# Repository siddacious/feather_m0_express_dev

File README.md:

# feather_m0_express_dev
Added two developer friendly features:
* SWD header for debugging
* SPI header for the on board SPI flash

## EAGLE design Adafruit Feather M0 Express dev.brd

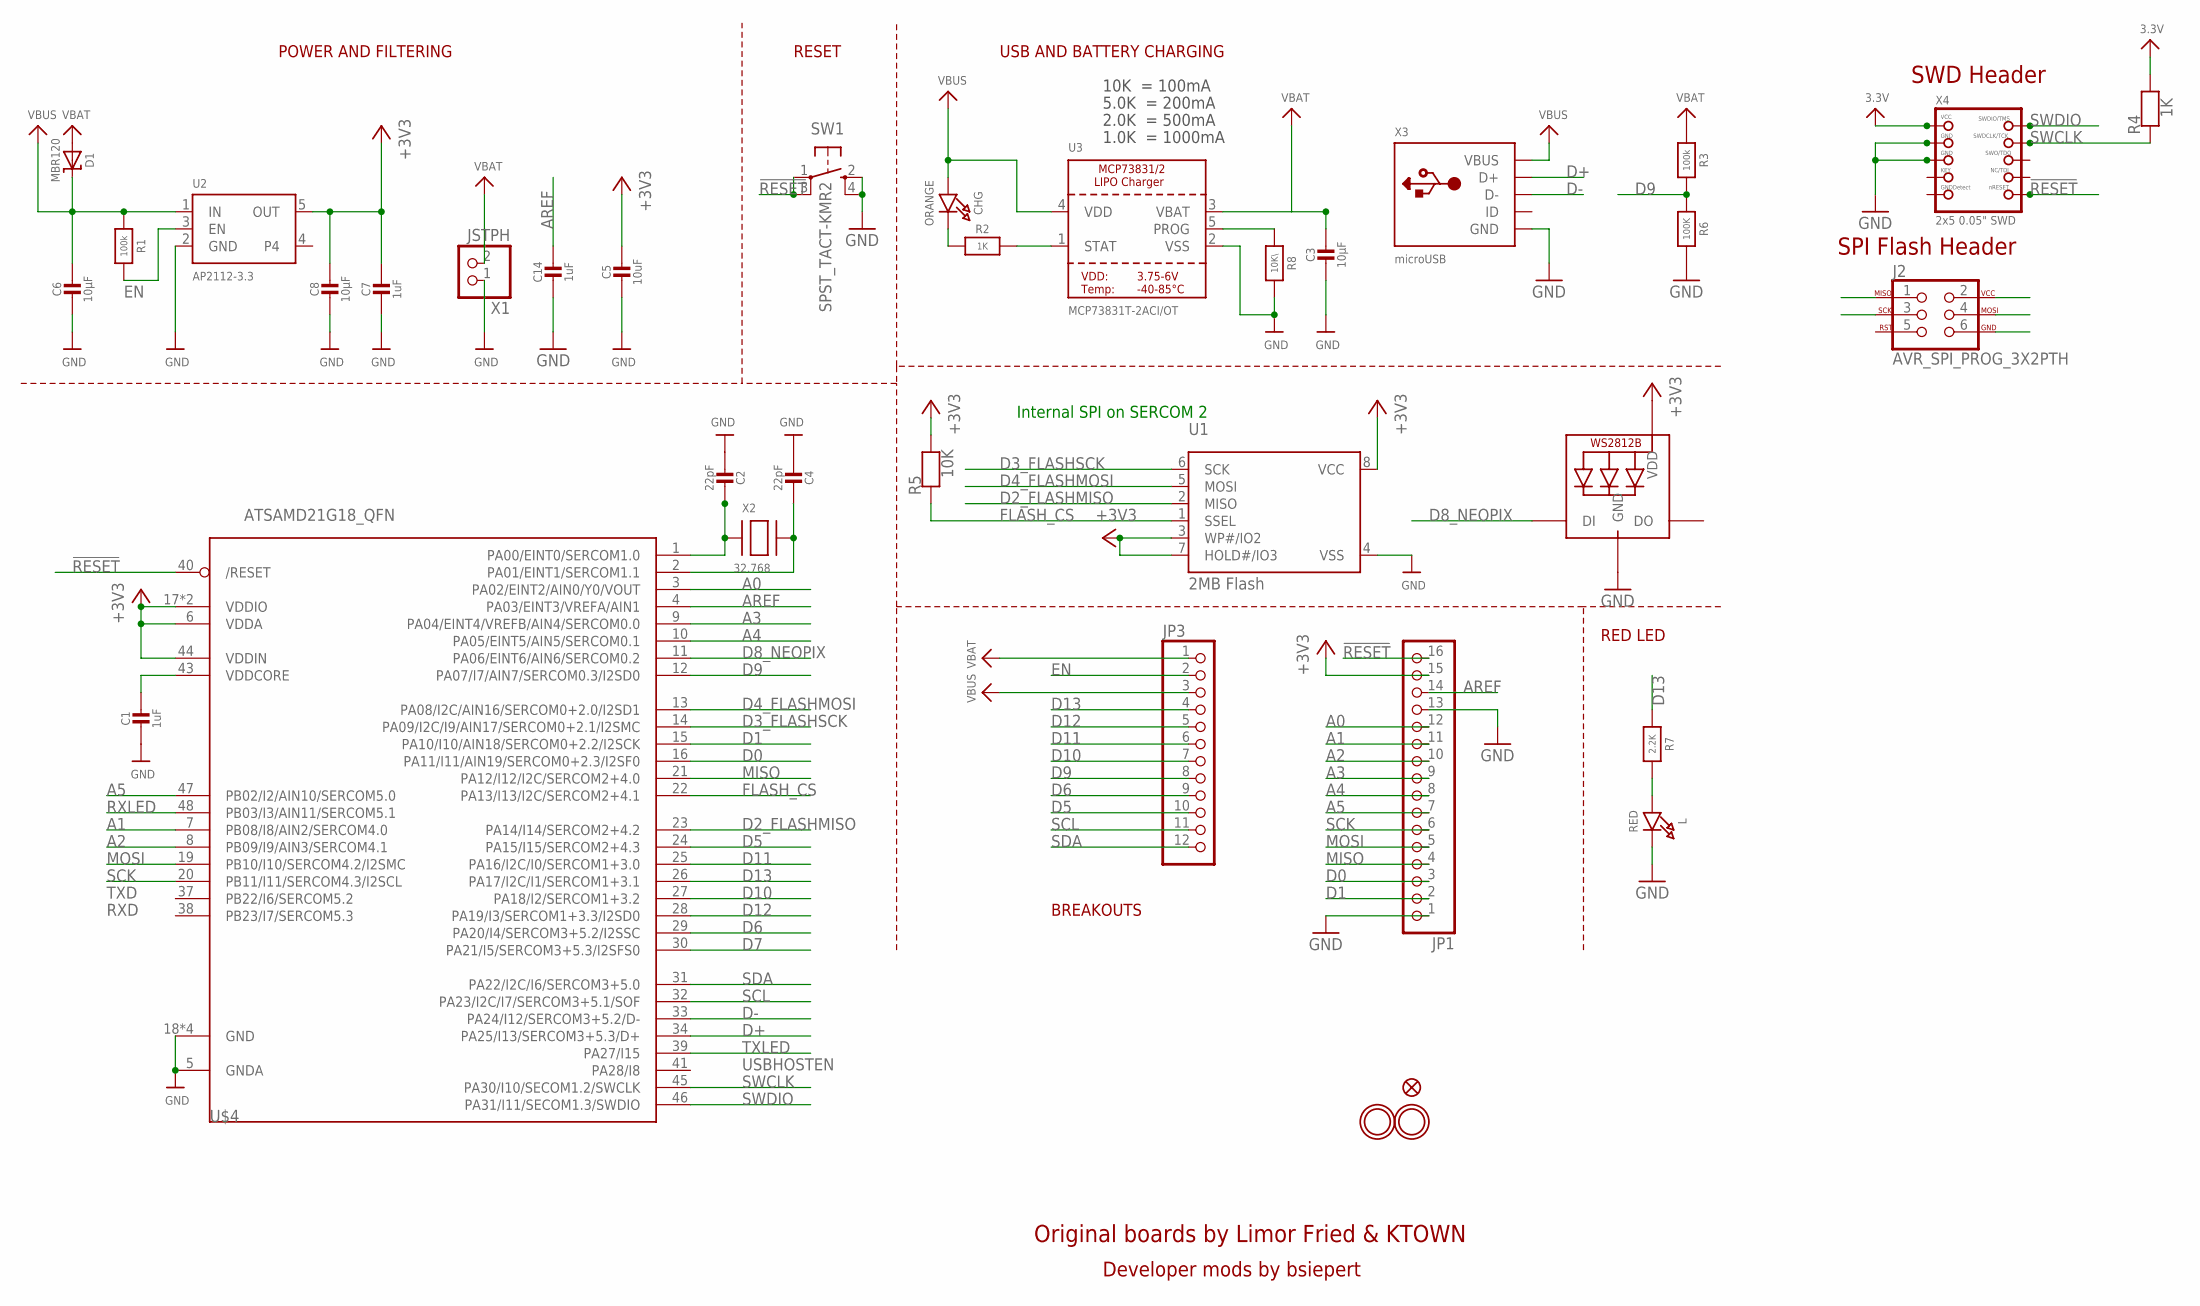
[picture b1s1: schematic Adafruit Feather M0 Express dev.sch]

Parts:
C1, C7, C14: 1uF; 0603-NO
C2, C4: 22pF; 0603-NO
C3, C6, C8: 10µF; 0805-NO
C5: 10uF; 0805-NO
CHG: ORANGE; CHIPLED_0805_NOOUTLINE
D1: MBR120; SOD-123
J2: AVR_SPI_PROG_3X2PTH; 2X3
JP1: HEADER-1X16ROUND; 1X16_ROUND
JP3: HEADER-1X12; 1X12_ROUND
L: RED; CHIPLED_0805_NOOUTLINE
LED1: WS2812B3535; LED3535
R1, R3: 100k; 0603-NO
R2: 1K; 0603-NO
R4: 1K; 0805-NO
R5: 10K; 0603-NO
R6: 100K; 0603-NO
R7: 2.2K; 0603-NO
R8: 10K\; 0603-NO
SW1: SPST_TACT-KMR2; KMR2
U1: 2MB Flash; SOIC8_208MIL
U2: AP2112-3.3; SOT23-5
U3: MCP73831T-2ACI/OT; SOT23-5
U$4: ATSAMD21G18_QFN; TQFN48_7MM
U$31, U$32: MOUNTINGHOLE2.5; MOUNTINGHOLE_2.5_PLATED
U$34: FIDUCIAL""; FIDUCIAL_1MM
X1: JSTPH; JSTPH2
X2: 32.768; XTAL3215
X3: microUSB; 4UCONN_20329_V2
X4: 2x5 0.05" SWD; 2X05_1.27MM_BOX_POSTS

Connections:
!RESET: JP1.16, SW1.1, SW1.3 (P1), U$4.40 (/RESET), X4.10 (NRESET)
+3V3: C5.1, C7.1, C8.1, J2.2, JP1.15, LED1.2 (VDD), R4.2, R5.2, U1.3 (WP#/IO2), U1.7 (HOLD#/IO3), U1.8 (VCC), U2.5 (OUT), U$4.6 (VDDA), U$4.17 (VDDIO), U$4.36 (VDDIO), U$4.44 (VDDIN), X4.1 (VCC)
A0: JP1.12, U$4.3 (PA02/EINT2/AIN0/Y0/VOUT)
A1: JP1.11, U$4.7 (PB08/I8/AIN2/SERCOM4.0)
A2: JP1.10, U$4.8 (PB09/I9/AIN3/SERCOM4.1)
A3: JP1.9, U$4.9 (PA04/EINT4/VREFB/AIN4/SERCOM0.0)
A4: JP1.8, U$4.10 (PA05/EINT5/AIN5/SERCOM0.1)
A5: JP1.7, U$4.47 (PB02/I2/AIN10/SERCOM5.0)
AREF: C14.1, JP1.14, U$4.4 (PA03/EINT3/VREFA/AIN1)
D0: JP1.3, U$4.16 (PA11/I11/AIN19/SERCOM0+2.3/I2SF0)
D1: JP1.2, U$4.15 (PA10/I10/AIN18/SERCOM0+2.2/I2SCK)
D2_FLASHMISO: J2.1, U1.2 (MISO), U$4.23 (PA14/I14/SERCOM2+4.2)
D3_FLASHSCK: J2.3, U1.6 (SCK), U$4.14 (PA09/I2C/I9/AIN17/SERCOM0+2.1/I2SMC)
D4_FLASHMOSI: J2.4, U1.5 (MOSI), U$4.13 (PA08/I2C/AIN16/SERCOM0+2.0/I2SD1)
D5: JP3.10, U$4.24 (PA15/I15/SERCOM2+4.3)
D6: JP3.9, U$4.29 (PA20/I4/SERCOM3+5.2/I2SSC)
D7: U$4.30 (PA21/I5/SERCOM3+5.3/I2SFS0)
D8_NEOPIX: LED1.1 (DI), U$4.11 (PA06/EINT6/AIN6/SERCOM0.2)
D9: JP3.8, R3.2, R6.1, U$4.12 (PA07/I7/AIN7/SERCOM0.3/I2SD0)
D10: JP3.7, U$4.27 (PA18/I2/SERCOM1+3.2)
D11: JP3.6, U$4.25 (PA16/I2C/I0/SERCOM1+3.0)
D12: JP3.5, U$4.28 (PA19/I3/SERCOM1+3.3/I2SD0)
D13: JP3.4, R7.1, U$4.26 (PA17/I2C/I1/SERCOM1+3.1)
D+: U$4.34 (PA25/I13/SERCOM3+5.3/D+), X3.D+
D-: U$4.33 (PA24/I12/SERCOM3+5.2/D-), X3.D-
EN: JP3.2, R1.2, U2.3 (EN)
FLASH_CS: R5.1, U1.1 (SSEL), U$4.22 (PA13/I13/I2C/SERCOM2+4.1)
GND: C1.2, C2.2, C3.2, C4.2, C5.2, C6.2, C7.2, C8.2, C14.2, J2.6, JP1.1, JP1.13, L.C, LED1.4 (GND), R6.2, R8.2, SW1.2 (S), SW1.4 (S1), U1.4 (VSS), U2.2 (GND), U3.2 (VSS), U$4.5 (GNDA), U$4.18 (GND), U$4.35 (GND), U$4.42 (GND), U$4.THERMAL (GND), X1.1, X3.BASE@1 (GND), X3.BASE@2 (GND), X3.GND, X3.SPRT@1 (GND), X3.SPRT@2 (GND), X3.SPRT@3 (GND), X3.SPRT@4 (GND), X4.3 (GND), X4.5 (GND)
MISO: JP1.4, U$4.21 (PA12/I12/I2C/SERCOM2+4.0)
MOSI: JP1.5, U$4.19 (PB10/I10/SERCOM4.2/I2SMC)
unnamed: CHG.C, R2.1
unnamed: L.A, R7.2
unnamed: R2.2, U3.1 (STAT)
unnamed: R8.1, U3.5 (PROG)
unnamed: C2.1, U$4.1 (PA00/EINT0/SERCOM1.0), X2.P$1
unnamed: C4.1, U$4.2 (PA01/EINT1/SERCOM1.1), X2.P$2
RXLED: U$4.48 (PB03/I3/AIN11/SERCOM5.1)
SCK: JP1.6, U$4.20 (PB11/I11/SERCOM4.3/I2SCL)
SCL: JP3.11, U$4.32 (PA23/I2C/I7/SERCOM3+5.1/SOF)
SDA: JP3.12, U$4.31 (PA22/I2C/I6/SERCOM3+5.0)
SWCLK: R4.1, U$4.45 (PA30/I10/SECOM1.2/SWCLK), X4.4 (SWDCLK)
SWDIO: U$4.46 (PA31/I11/SECOM1.3/SWDIO), X4.2 (SWDIO)
TXLED: U$4.39 (PA27/I15)
VBAT: C3.1, D1.A, JP3.1, R3.1, U3.3 (VBAT), X1.2
VBUS: C6.1, CHG.A, D1.C, JP3.3, R1.1, U2.1 (IN), U3.4 (VDD), X3.VBUS
VDDCORE: C1.1, U$4.43 (VDDCORE)

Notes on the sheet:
POWER AND FILTERING
RESET
10K = 100mA
5.0K = 200mA
2.0K = 500mA
1.0K = 1000mA
USBHOSTEN
TXD
RXD
USB AND BATTERY CHARGING
BREAKOUTS
RED LED
Internal SPI on SERCOM 2
Original boards by Limor Fried & KTOWN
SWD Header
Developer mods by bsiepert
SPI Flash Header

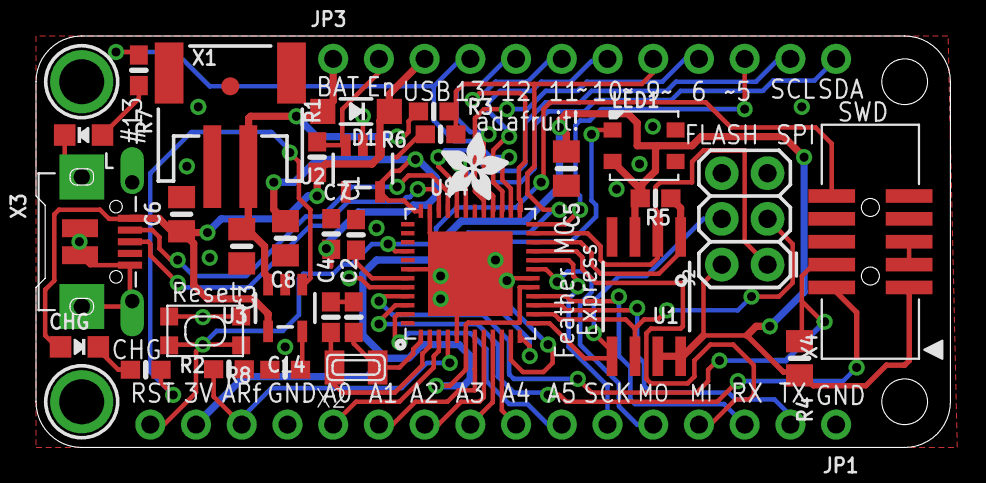
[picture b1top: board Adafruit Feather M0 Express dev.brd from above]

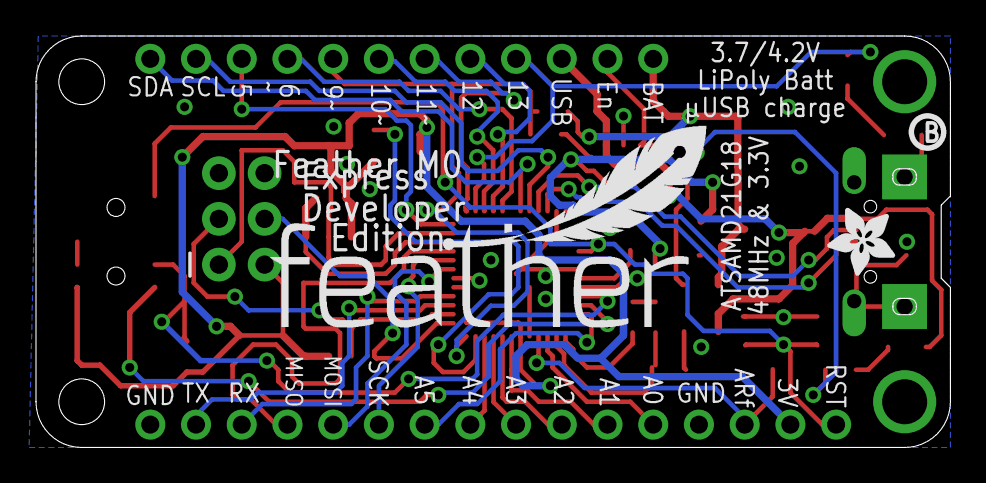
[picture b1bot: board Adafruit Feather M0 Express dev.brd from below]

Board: 2 copper layers, 50.8 x 22.9 mm, 40 parts (3 on the bottom side), 43 nets.

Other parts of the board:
U$7, U$12: ADAFRUIT_3.5MM
U$9: FEATHERLOGO
U$13: PCBFEAT-REV-040

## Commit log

2017-09-21 inital rev of board & schematic with numerous angle DRC errors
2017-09-21 README.md updated
2017-09-21 fixed all bottom layer DRC errors
2017-09-21 fixed top angle DRCs. One bad overlap left
2017-09-21 last bad overlap fixed! Still unsure about the bottom layer groundplane under the +3v3 end of C7
2017-09-21 fixed up silkscreen

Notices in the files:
parts and their libraries:
microbuilder: This work is placed in the public domain, and may be freely used for commercial and non-commercial work with the following conditions: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
SparkFun-Connectors: Licensing: Creative Commons ShareAlike 4.0 International - https://creativecommons.org/licenses/by-sa/4.0
